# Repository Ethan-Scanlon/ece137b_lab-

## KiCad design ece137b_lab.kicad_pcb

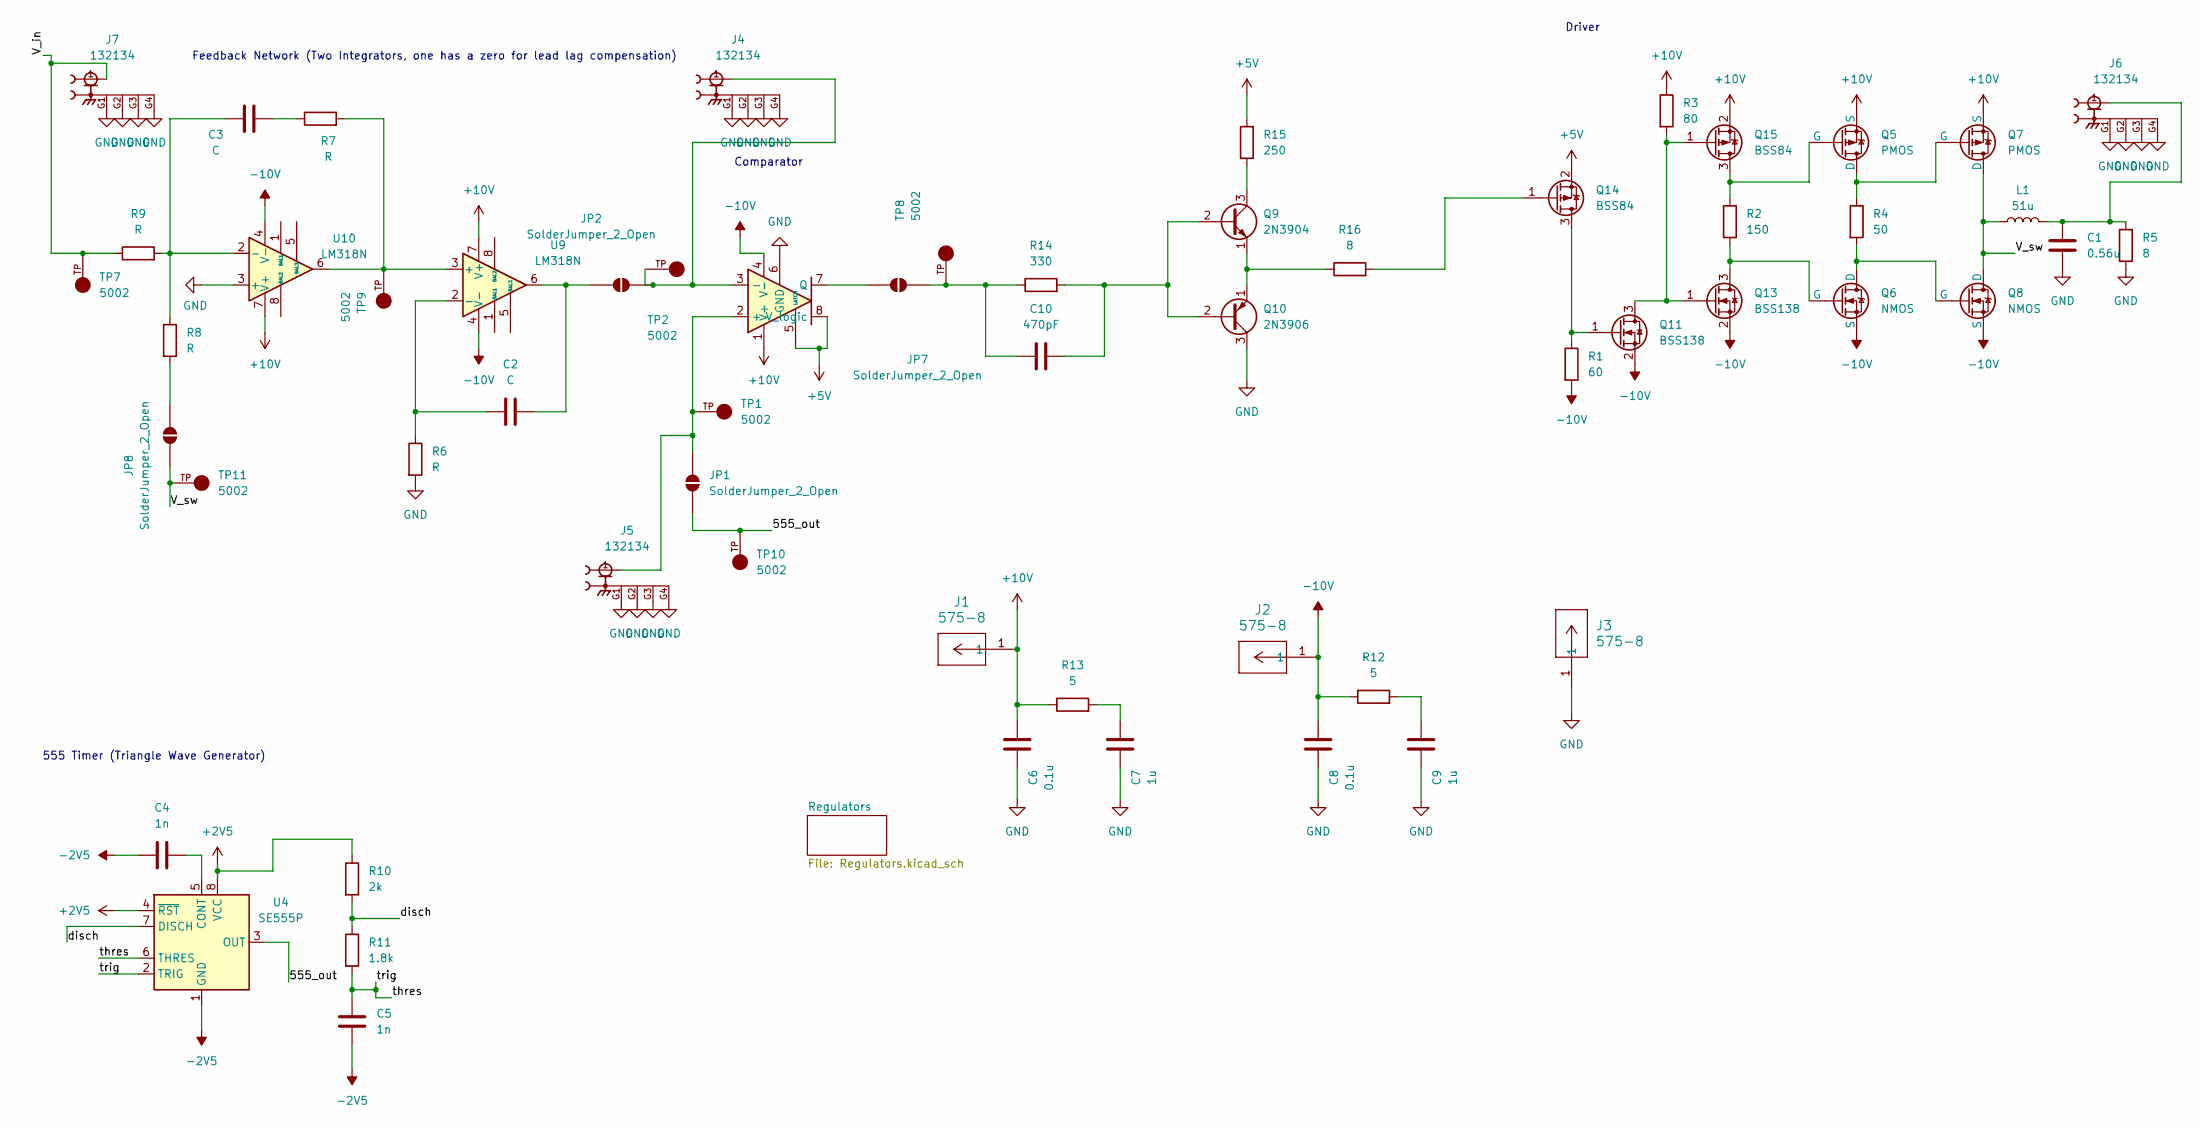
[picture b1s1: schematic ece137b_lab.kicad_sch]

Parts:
C1: 0.56u; C_Rect_L10.0mm_W4.0mm_P7.50mm_FKS3_FKP3
C2, C3: C; C_Radial_D6.3mm_H5.0mm_P2.50mm
C4, C5: 1n; C_Radial_D6.3mm_H5.0mm_P2.50mm
C6, C8: 0.1u; C_Radial_D6.3mm_H5.0mm_P2.50mm
C7, C9: 1u; C_Radial_D6.3mm_H5.0mm_P2.50mm
C10: 470pF; C_Radial_D6.3mm_H5.0mm_P2.50mm
J1, J2, J3: 575-8; CONN_575-8_KEY
J4, J5, J6, J7: 132134; AMPHENOL_132134; PARTREV E
JP1, JP2, JP7, JP8: SolderJumper_2_Open; SolderJumper-2_P1.3mm_Open_Pad1.0x1.5mm
L1: 51u; CTX50-1-52-R
Q5, Q7: PMOS; TO-251-3_Vertical
Q6, Q8: NMOS; TO-251-3_Vertical
Q9: 2N3904; TO-92_Inline
Q10: 2N3906; TO-92_Inline
Q11, Q13: BSS138; SOT-23
Q14, Q15: BSS84; SOT-23
R1: 60; R_Axial_DIN0207_L6.3mm_D2.5mm_P10.16mm_Horizontal
R2: 150; R_Axial_DIN0207_L6.3mm_D2.5mm_P10.16mm_Horizontal
R3: 80; R_Axial_DIN0207_L6.3mm_D2.5mm_P10.16mm_Horizontal
R4: 50; R_Axial_DIN0207_L6.3mm_D2.5mm_P10.16mm_Horizontal
R5: 8; TO-220-2_Vertical
R6, R7, R8, R9: R; R_Axial_DIN0207_L6.3mm_D2.5mm_P10.16mm_Horizontal
R10: 2k; R_Axial_DIN0207_L6.3mm_D2.5mm_P10.16mm_Horizontal
R11: 1.8k; R_Axial_DIN0207_L6.3mm_D2.5mm_P10.16mm_Horizontal
R12, R13: 5; R_Axial_DIN0207_L6.3mm_D2.5mm_P10.16mm_Horizontal
R14: 330; R_Axial_DIN0207_L6.3mm_D2.5mm_P10.16mm_Horizontal
R15: 250; R_Axial_DIN0207_L6.3mm_D2.5mm_P10.16mm_Horizontal
R16: 8; R_Axial_DIN0207_L6.3mm_D2.5mm_P10.16mm_Horizontal
TP1, TP2, TP7, TP8, TP9, TP10, TP11: 5002; KEYSTONE_5002; PARTREV H
U1: DIP-8_W7.62mm
U4: SE555P; DIP-8_W7.62mm
U9, U10: LM318N; N08E

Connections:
+2V5: R10.1, U4.4 (~RST), U4.8 (VCC); also elsewhere on the board
+5V: Q14.2 (S), R15.2, U1.5 (LATCH), U1.8 (V_logic); also elsewhere on the board
+10V: C6.2, J1.1 (1_1), Q5.3 (S), Q7.3 (S), Q15.2 (S), R3.1, R13.1, U1.1 (V+), U9.7 (V+), U10.7 (V+); also elsewhere on the board
-2V5: C4.1, C5.2, U4.1 (GND); also elsewhere on the board
-10V: C8.2, J2.1 (1_1), Q6.3 (S), Q8.3 (S), Q11.2 (S), Q13.2 (S), R1.2, R12.1, U1.4 (V-), U9.4 (V-), U10.4 (V-); also elsewhere on the board
/555_out: JP1.1 (A), TP10.TP, U4.3 (OUT)
/V_in: J7.1, R9.1, TP7.TP
/V_sw: JP8.2 (B), L1.1, Q7.1 (D), Q8.1 (D), TP11.TP
/disch: R10.2, R11.1, U4.7 (DISCH)
/thres: C5.1, R11.2, U4.2 (TRIG), U4.6 (THRES)
GND: C1.2, C6.1, C7.1, C8.1, C9.1, J3.1 (1_1), J4.G1, J4.G2, J4.G3, J4.G4, J5.G1, J5.G2, J5.G3, J5.G4, J6.G1, J6.G2, J6.G3, J6.G4, J7.G1, J7.G2, J7.G3, J7.G4, Q10.3 (C), R5.2, R6.2, U1.6 (GND), U10.3 (+); also elsewhere on the board
unnamed: C1.1, J6.1, L1.2, R5.1
unnamed: C3.2, R7.1
unnamed: C7.2, R13.2
unnamed: C9.2, R12.2
unnamed: J5.1, JP1.2 (B), TP1.TP, U1.2 (+)
unnamed: J4.1, JP2.1 (A), TP2.TP, U1.3 (-)
unnamed: C2.1, JP2.2 (B), U9.6
unnamed: C10.2, JP7.1 (A), R14.1, TP8.TP
unnamed: JP7.2 (B), U1.7 (Q)
unnamed: JP8.1 (A), R8.2
unnamed: Q5.1 (D), Q7.2 (G), R4.1
unnamed: Q6.1 (D), Q8.2 (G), R4.2
unnamed: Q9.3 (C), R15.1
unnamed: C10.1, Q9.2 (B), Q10.2 (B), R14.2
unnamed: Q9.1 (E), Q10.1 (E), R16.1
unnamed: Q11.3 (D), Q13.1 (G), Q15.1 (G), R3.2
unnamed: Q11.1 (G), Q14.3 (D), R1.1
unnamed: Q6.2 (G), Q13.3 (D), R2.2
unnamed: Q14.1 (G), R16.2
unnamed: Q5.2 (G), Q15.3 (D), R2.1
unnamed: C4.2, U4.5 (CONT)
unnamed: R7.2, TP9.TP, U9.3 (+), U10.6
unnamed: C2.2, R6.1, U9.2 (-)
unnamed: C3.1, R8.1, R9.2, U10.2 (-)

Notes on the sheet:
Comparator
Feedback Network (Two Integrators, one has a zero for lead lag compensation)
555 Timer (Triangle Wave Generator)
Driver

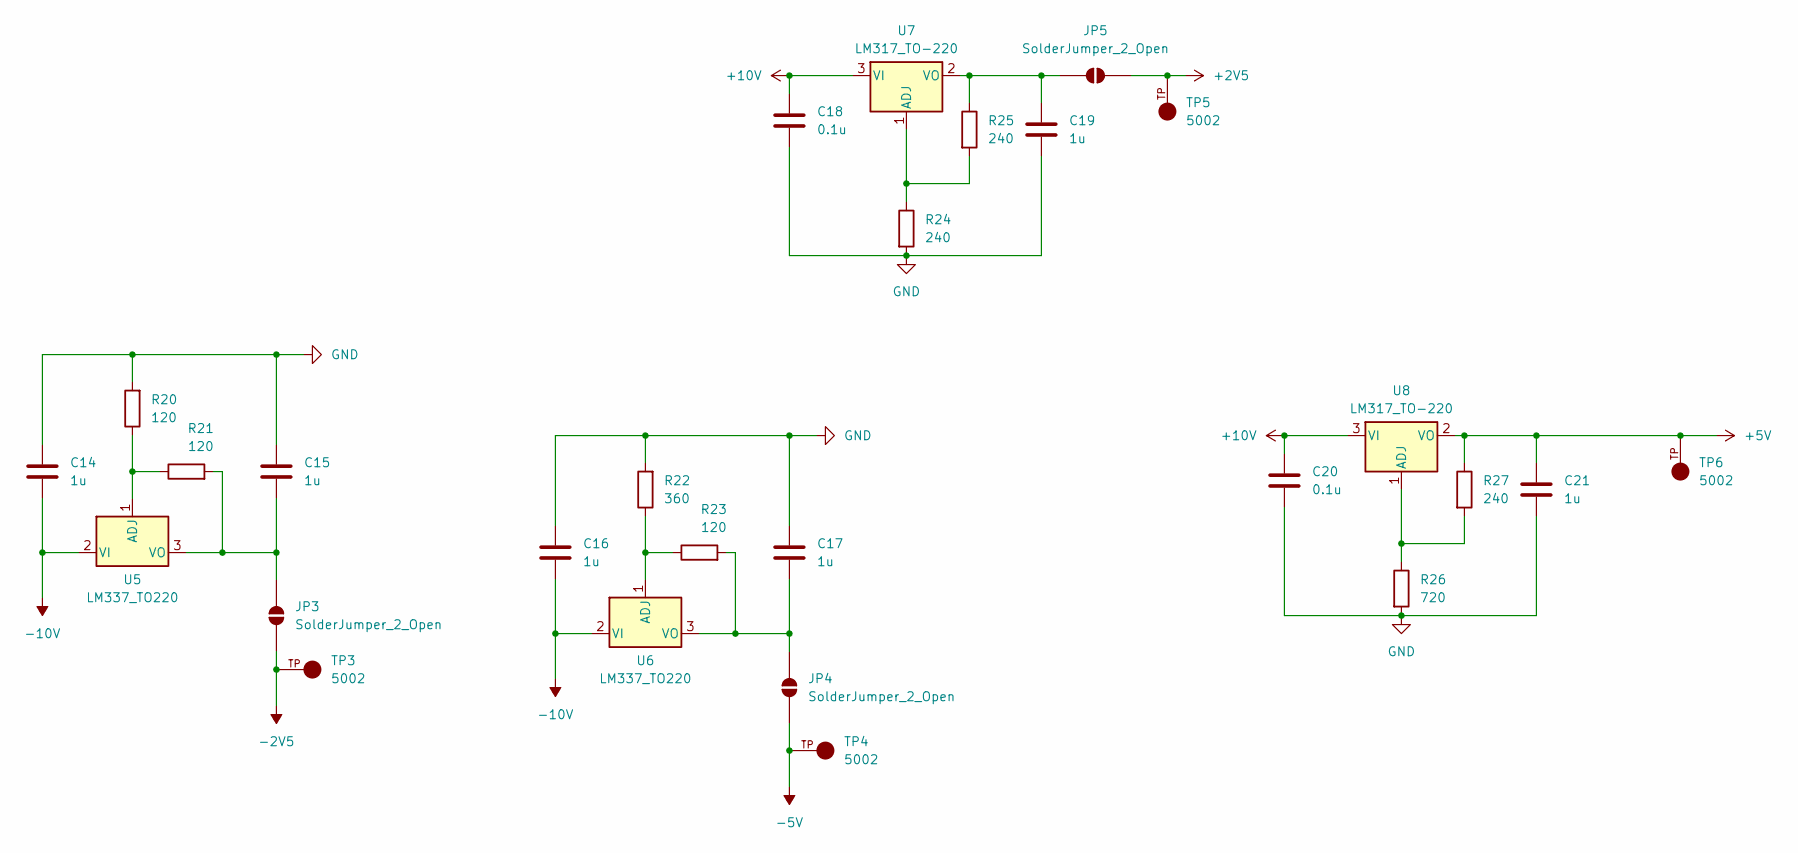
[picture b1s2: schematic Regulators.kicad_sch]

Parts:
C14, C15, C16, C17, C19, C21: 1u; C_Radial_D6.3mm_H5.0mm_P2.50mm
C18, C20: 0.1u; C_Radial_D6.3mm_H5.0mm_P2.50mm
JP3, JP4, JP5: SolderJumper_2_Open; SolderJumper-2_P1.3mm_Open_Pad1.0x1.5mm
R20, R21, R23: 120; R_Axial_DIN0207_L6.3mm_D2.5mm_P10.16mm_Horizontal
R22: 360; R_Axial_DIN0207_L6.3mm_D2.5mm_P10.16mm_Horizontal
R24, R25, R27: 240; R_Axial_DIN0207_L6.3mm_D2.5mm_P10.16mm_Horizontal
R26: 720; R_Axial_DIN0207_L6.3mm_D2.5mm_P10.16mm_Horizontal
TP3, TP4, TP5, TP6: 5002; KEYSTONE_5002; PARTREV H
U5, U6: LM337_TO220; TO-220-3_Vertical
U7, U8: LM317_TO-220; TO-220-3_Vertical

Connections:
+2V5: JP5.1 (A), TP5.TP; also elsewhere on the board
+5V: C21.2, R27.1, TP6.TP, U8.2 (VO); also elsewhere on the board
+10V: C18.2, C20.2, U7.3 (VI), U8.3 (VI); also elsewhere on the board
-2V5: JP3.1 (A), TP3.TP; also elsewhere on the board
-5V: JP4.1 (A), TP4.TP
-10V: C14.1, C16.1, U5.2 (VI), U6.2 (VI); also elsewhere on the board
GND: C14.2, C15.2, C16.2, C17.2, C18.1, C19.1, C20.1, C21.1, R20.2, R22.2, R24.2, R26.2; also elsewhere on the board
unnamed: C15.1, JP3.2 (B), R21.2, U5.3 (VO)
unnamed: C17.1, JP4.2 (B), R23.2, U6.3 (VO)
unnamed: C19.2, JP5.2 (B), R25.1, U7.2 (VO)
unnamed: R20.1, R21.1, U5.1 (ADJ)
unnamed: R22.1, R23.1, U6.1 (ADJ)
unnamed: R24.1, R25.2, U7.1 (ADJ)
unnamed: R26.1, R27.2, U8.1 (ADJ)

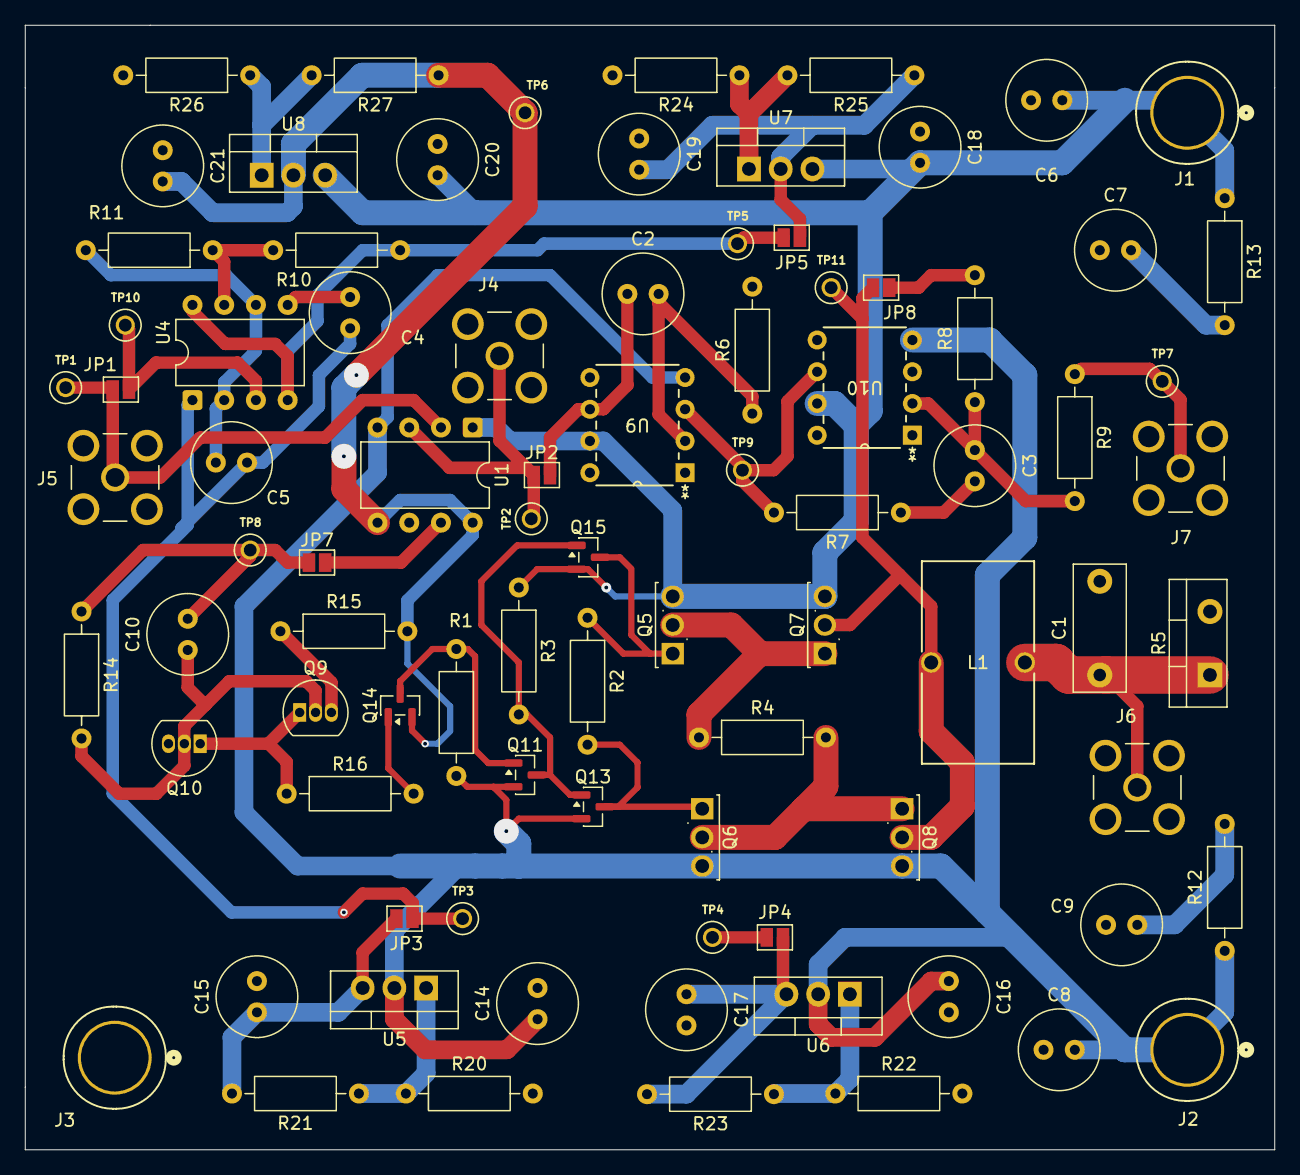
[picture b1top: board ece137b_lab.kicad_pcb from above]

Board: 4 copper layers, 100.0 x 90.0 mm, 86 parts (0 on the bottom side), 43 nets.

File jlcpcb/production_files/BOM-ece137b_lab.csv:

Comment,Designator,Footprint,LCSC,Quantity
5002,TP7,KEYSTONE_5002,,1
LM337_TO220,U5,TO-220-3_Vertical,,1
5002,TP3,KEYSTONE_5002,,1
5002,TP1,KEYSTONE_5002,,1
575-8,J2,CONN_575-8_KEY,,1
5002,TP9,KEYSTONE_5002,,1
0.1u,C8,C_Radial_D6.3mm_H5.0mm_P2.50mm,,1
NMOS,Q8,TO-251-3_Vertical,,1
R,R8,R_Axial_DIN0207_L6.3mm_D2.5mm_P10.16mm_Horizontal,,1
80,R3,R_Axial_DIN0207_L6.3mm_D2.5mm_P10.16mm_Horizontal,,1
150,R2,R_Axial_DIN0207_L6.3mm_D2.5mm_P10.16mm_Horizontal,,1
132134,J4,AMPHENOL_132134,,1
51u,L1,CTX50-1-52-R,,1
0.1u,C20,C_Radial_D6.3mm_H5.0mm_P2.50mm,,1
132134,J7,AMPHENOL_132134,,1
240,R27,R_Axial_DIN0207_L6.3mm_D2.5mm_P10.16mm_Horizontal,,1
1u,C7,C_Radial_D6.3mm_H5.0mm_P2.50mm,,1
C,C3,C_Radial_D6.3mm_H5.0mm_P2.50mm,,1
120,R21,R_Axial_DIN0207_L6.3mm_D2.5mm_P10.16mm_Horizontal,,1
0.1u,C18,C_Radial_D6.3mm_H5.0mm_P2.50mm,,1
5002,TP8,KEYSTONE_5002,,1
1u,C15,C_Radial_D6.3mm_H5.0mm_P2.50mm,,1
5,R12,R_Axial_DIN0207_L6.3mm_D2.5mm_P10.16mm_Horizontal,,1
1.8k,R11,R_Axial_DIN0207_L6.3mm_D2.5mm_P10.16mm_Horizontal,,1
575-8,J1,CONN_575-8_KEY,,1
1u,C14,C_Radial_D6.3mm_H5.0mm_P2.50mm,,1
5002,TP6,KEYSTONE_5002,,1
5002,TP4,KEYSTONE_5002,,1
240,R25,R_Axial_DIN0207_L6.3mm_D2.5mm_P10.16mm_Horizontal,,1
360,R22,R_Axial_DIN0207_L6.3mm_D2.5mm_P10.16mm_Horizontal,,1
R,R9,R_Axial_DIN0207_L6.3mm_D2.5mm_P10.16mm_Horizontal,,1
LM318N,U9,N08E,,1
240,R24,R_Axial_DIN0207_L6.3mm_D2.5mm_P10.16mm_Horizontal,,1
5,R13,R_Axial_DIN0207_L6.3mm_D2.5mm_P10.16mm_Horizontal,,1
PMOS,Q7,TO-251-3_Vertical,,1
720,R26,R_Axial_DIN0207_L6.3mm_D2.5mm_P10.16mm_Horizontal,,1
5002,TP5,KEYSTONE_5002,,1
1u,C17,C_Radial_D6.3mm_H5.0mm_P2.50mm,,1
132134,J5,AMPHENOL_132134,,1
5002,TP11,KEYSTONE_5002,,1
0.1u,C6,C_Radial_D6.3mm_H5.0mm_P2.50mm,,1
R,R6,R_Axial_DIN0207_L6.3mm_D2.5mm_P10.16mm_Horizontal,,1
50,R4,R_Axial_DIN0207_L6.3mm_D2.5mm_P10.16mm_Horizontal,,1
120,R23,R_Axial_DIN0207_L6.3mm_D2.5mm_P10.16mm_Horizontal,,1
2k,R10,R_Axial_DIN0207_L6.3mm_D2.5mm_P10.16mm_Horizontal,,1
8,R5,TO-220-2_Vertical,,1
SE555P,U4,DIP-8_W7.62mm,,1
LM337_TO220,U6,TO-220-3_Vertical,,1
C,C2,C_Radial_D6.3mm_H5.0mm_P2.50mm,,1
0.56u,C1,C_Rect_L10.0mm_W4.0mm_P7.50mm_FKS3_FKP3,,1
LM317_TO-220,U7,TO-220-3_Vertical,,1
5002,TP2,KEYSTONE_5002,,1
NMOS,Q6,TO-251-3_Vertical,,1
1u,C9,C_Radial_D6.3mm_H5.0mm_P2.50mm,,1
60,R1,R_Axial_DIN0207_L6.3mm_D2.5mm_P10.16mm_Horizontal,,1
~,U1,DIP-8_W7.62mm,,1
1n,C4,C_Radial_D6.3mm_H5.0mm_P2.50mm,,1
PMOS,Q5,TO-251-3_Vertical,,1
LM317_TO-220,U8,TO-220-3_Vertical,,1
1n,C5,C_Radial_D6.3mm_H5.0mm_P2.50mm,,1
R,R7,R_Axial_DIN0207_L6.3mm_D2.5mm_P10.16mm_Horizontal,,1
1u,C19,C_Radial_D6.3mm_H5.0mm_P2.50mm,,1
120,R20,R_Axial_DIN0207_L6.3mm_D2.5mm_P10.16mm_Horizontal,,1
132134,J6,AMPHENOL_132134,,1
1u,C21,C_Radial_D6.3mm_H5.0mm_P2.50mm,,1
5002,TP10,KEYSTONE_5002,,1
575-8,J3,CONN_575-8_KEY,,1
LM318N,U10,N08E,,1
1u,C16,C_Radial_D6.3mm_H5.0mm_P2.50mm,,1
2N3904,Q9,TO-92_Inline,,1
2N3906,Q10,TO-92_Inline,,1
250,R15,R_Axial_DIN0207_L6.3mm_D2.5mm_P10.16mm_Horizontal,,1
8,R16,R_Axial_DIN0207_L6.3mm_D2.5mm_P10.16mm_Horizontal,,1
470pF,C10,C_Radial_D6.3mm_H5.0mm_P2.50mm,,1
330,R14,R_Axial_DIN0207_L6.3mm_D2.5mm_P10.16mm_Horizontal,,1
BSS84,Q15,SOT-23,,1
BSS84,Q14,SOT-23,,1
BSS138,Q13,SOT-23,,1
BSS138,Q11,SOT-23,,1

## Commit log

2026-04-22 add sym footprint and lib folders
2026-05-11 hahaha
